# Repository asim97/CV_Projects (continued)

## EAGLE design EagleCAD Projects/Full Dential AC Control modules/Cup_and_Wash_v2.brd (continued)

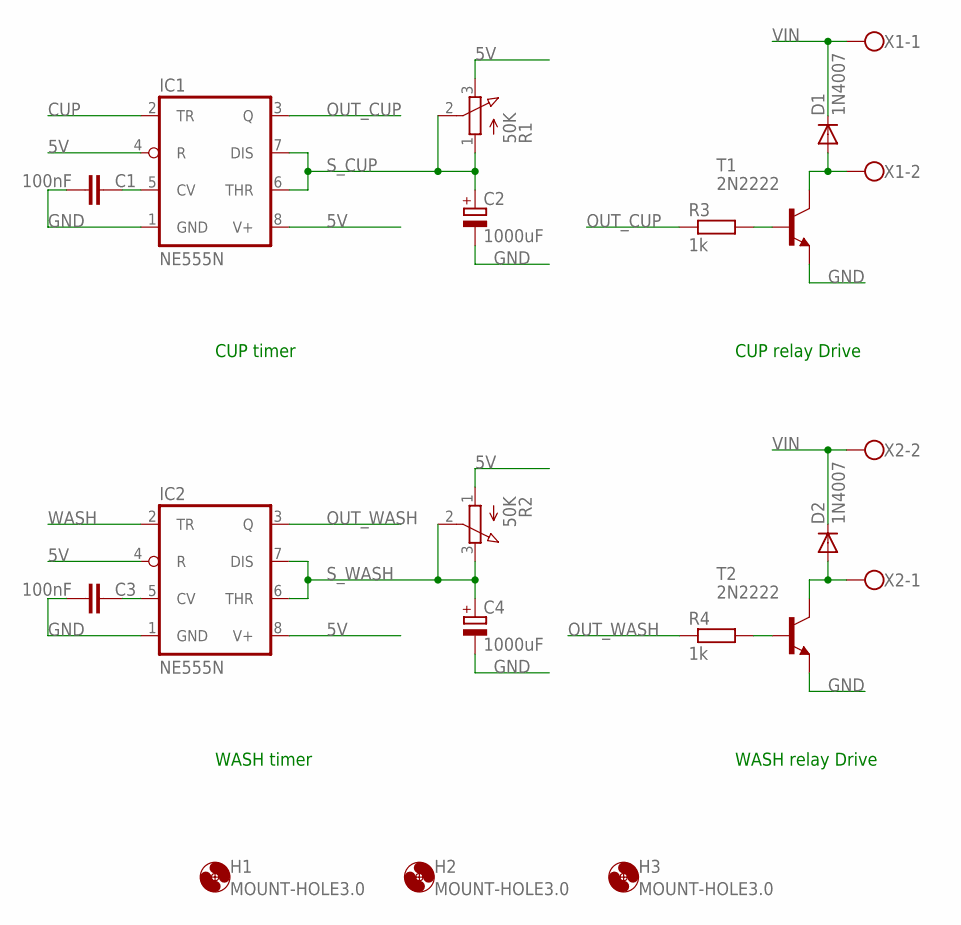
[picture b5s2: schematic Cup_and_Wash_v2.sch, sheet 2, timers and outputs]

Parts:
C1, C3: 100nF; C050-025X075
C2, C4: 1000uF; E5-13
D1, D2: 1N4007; DO41-10
H1, H2, H3: MOUNT-HOLE3.0; 3,0
IC1, IC2: NE555N; DIL08-ROUND
R1, R2: 50K; 3RP/1610N
R3, R4: 1k; 0207/10
T1, T2: 2N2222; TO92-EBC-OVAL
X1, X2: W237-102

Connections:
5V: IC1.4 (R), IC1.8 (V+), IC2.4 (R), IC2.8 (V+), R1.3 (E), R2.1 (A); also elsewhere on the board
CUP: IC1.2 (TR); also elsewhere on the board
GND: C1.2, C2.-, C3.2, C4.-, IC1.1 (GND), IC2.1 (GND), T1.E, T2.E; also elsewhere on the board
unnamed: D1.A, T1.C, X1.2
unnamed: C1.1, IC1.5 (CV)
unnamed: C3.1, IC2.5 (CV)
unnamed: D2.A, T2.C, X2.1
unnamed: R3.2, T1.B
unnamed: R4.2, T2.B
OUT_CUP: IC1.3 (Q), R3.1
OUT_WASH: IC2.3 (Q), R4.1
S_CUP: C2.+, IC1.6 (THR), IC1.7 (DIS), R1.1 (A), R1.2 (S)
S_WASH: C4.+, IC2.6 (THR), IC2.7 (DIS), R2.2 (S), R2.3 (E)
VIN: D1.C, D2.C, X1.1, X2.2; also elsewhere on the board
WASH: IC2.2 (TR); also elsewhere on the board

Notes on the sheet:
CUP timer
CUP relay Drive
WASH timer
WASH relay Drive

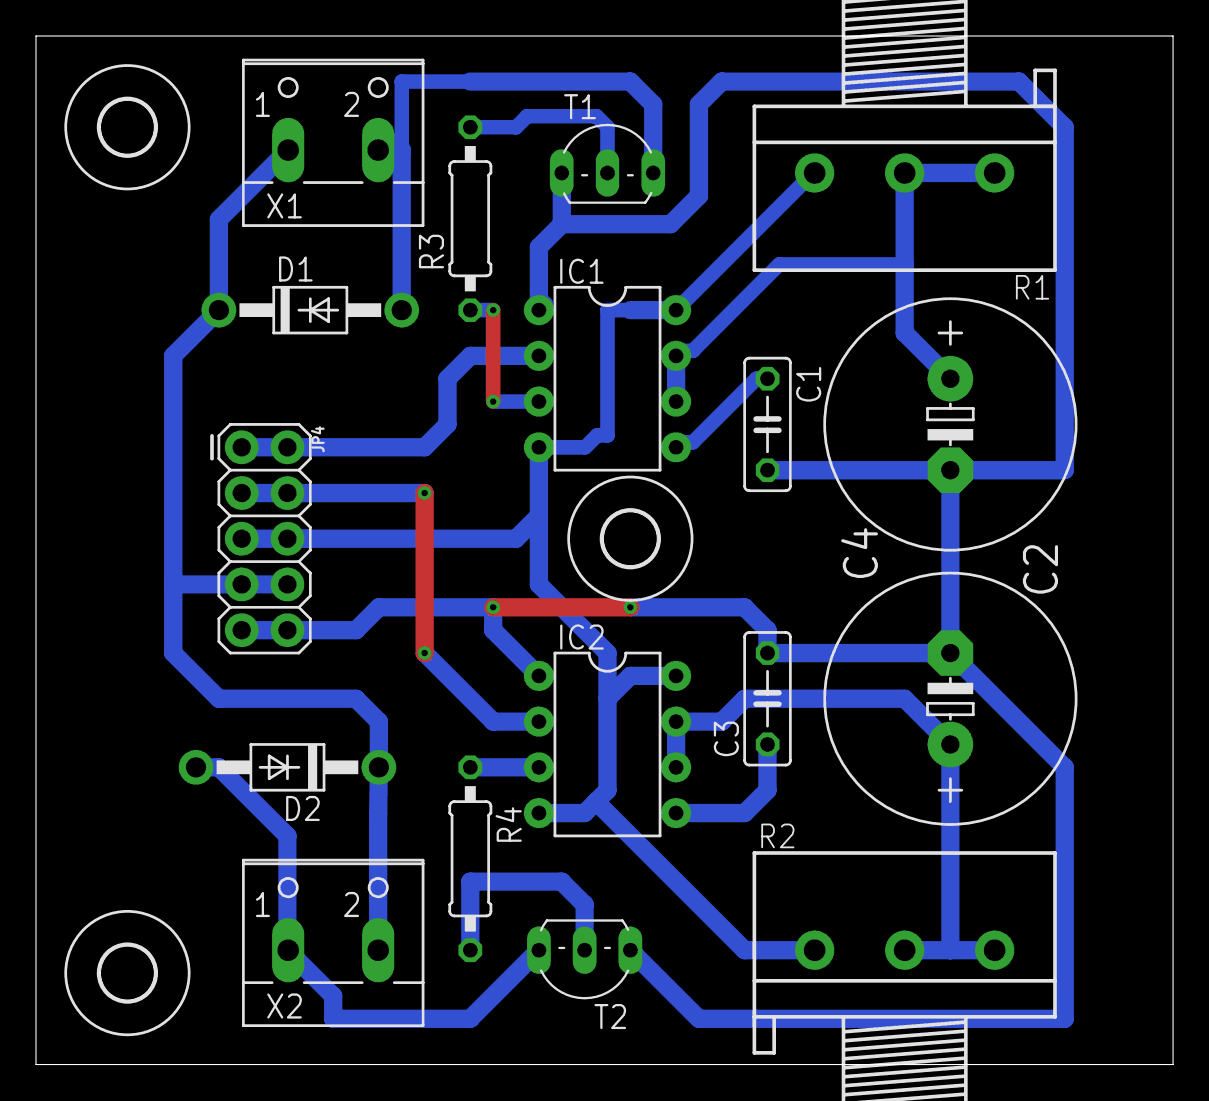
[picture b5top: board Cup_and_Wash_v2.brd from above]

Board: 2 copper layers, 63.2 x 57.1 mm, 20 parts (0 on the bottom side), 15 nets.

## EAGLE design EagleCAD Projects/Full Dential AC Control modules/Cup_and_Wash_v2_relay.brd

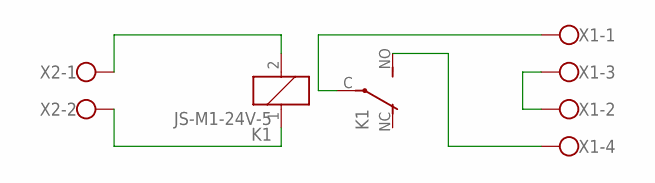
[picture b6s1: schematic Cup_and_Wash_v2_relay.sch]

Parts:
K1: JS-M1-24V-5; JS-M
X1: W237-4
X2: W237-102

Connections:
unnamed: K1.2, X2.1
unnamed: K1.1, X2.2
unnamed: K1.C, X1.1
unnamed: X1.2, X1.3
unnamed: K1.NO (S), X1.4

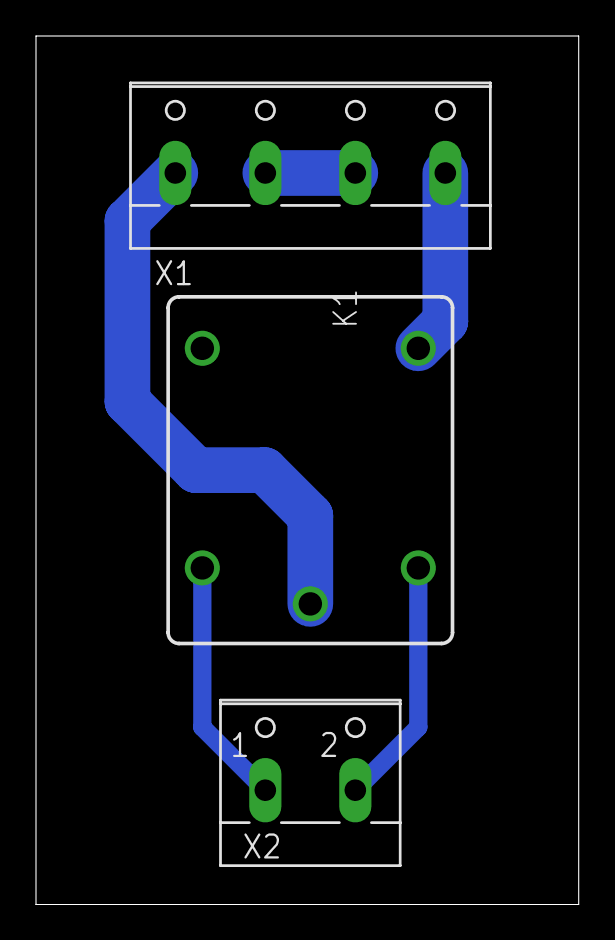
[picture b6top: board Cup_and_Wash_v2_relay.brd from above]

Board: 2 copper layers, 30.1 x 48.2 mm, 3 parts (0 on the bottom side), 5 nets.
